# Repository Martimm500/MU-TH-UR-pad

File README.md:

# MU / TH / UR Pad

A 16 Key Macropad dedicated to honoring the ALIEN Franchise...

and also day to day use :)

This is my first ever contact with PCB design but still I wanted to make something professional and that would push all my skills, including the coding ones forward.

I set out on making the design resemble MU / TH / UR from the ALIEN Movies and games (hence the retro look).

**For more info about the design process check out my [Development Journal](https://blueprint.hackclub.com/projects/13398) or the [Markdown Backup](https://github.com/Martimm500/MU-TH-UR-pad/blob/main/mu-th-ur-pad-journal.md) of it!**

## Design

First it's extremely important to notice **I was heavily inspired by Orpheuspad** (literally as soon as I saw it I said "I gotta make something like this"), 

Second my goal was not to copy Orpheuspad, it was to make a PCB from the ground up, but keeping what the thing I really liked in the Orpheuspad case, I fixed some errors I encountered in it's 3D model, and adjusted some details to my preference.

The final product turned out as a **16 Key Macropad featuring an OLED Screen, a Rotary Encoder and 2 LEDs**. The left side of the case is a Orpheuspad Fix and Improvement while making the style a little bit more **retro**, and the right side is merely and expansion upon that.

The colors of the case resemble MU / TH / UR (and honestly those old office keyboards lol)

Finnally I added a Dither Art of a facehugger strangling a person on the back of the PCB as well as some references to the movies and the famous ALIEN slogan.

## BOM Table

Also available as a CSV file [BOM.csv](https://github.com/ppppp)!

|ITEM                                                                                                                                                                                                                                                                                                                                                                                                                                                                                                                                                                                                                                                                                                                                          |QTY                       |UNIT PRICE (USD)|TOTAL PRICE + SHIPPING + TAX (USD)|LINK                               |
|----------------------------------------------------------------------------------------------------------------------------------------------------------------------------------------------------------------------------------------------------------------------------------------------------------------------------------------------------------------------------------------------------------------------------------------------------------------------------------------------------------------------------------------------------------------------------------------------------------------------------------------------------------------------------------------------------------------------------------------------|--------------------------|----------------|----------------------------------|-----------------------------------|
|WAVESHARE  RP2040-Zero                                                                                                                                                                                                                                                                                                                                                                                                                                                                                                                                                                                                                                                                                                                        |1                         |3,99            |9,99                              |https://www.waveshare.com/rp2040-zero.htm?sku=20187|
|PCB                                                                                                                                                                                                                                                                                                                                                                                                                                                                                                                                                                                                                                                                                                                                           |1                         |29,6            |36,2                              |https://www.pcbway.com/            |
|0.91in OLED Display                                                                                                                                                                                                                                                                                                                                                                                                                                                                                                                                                                                                                                                                                                                           |1                         |4,05            |4,05                              |https://mauser.pt/096-8736/display-lcd-oled-0-91-128x32-ssd1306-branco|
|SK6812 MINI-E LEDs                                                                                                                                                                                                                                                                                                                                                                                                                                                                                                                                                                                                                                                                                                                            |10                 (minimum amount)|2,80            |3,00                              |https://pt.aliexpress.com/item/1005005237439694.html?spm=a2g0o.cart.0.0.f20f7f06EaY2LD&mp=1&pdp_npi=6%40dis%21EUR%21EUR%203.31%21EUR%202.42%21%21EUR%200.01%21%21%21%40211b612817743682508285298e4c09%2112000034757484069%21ct%21PT%214870840647%21%211%210%21&gatewayAdapt=glo2bra|
|M3x16mm Screws                                                                                                                                                                                                                                                                                                                                                                                                                                                                                                                                                                                                                                                                                                                                |10                        |2,43            |3,30                              |https://pt.aliexpress.com/item/1005008062349572.html?spm=a2g0o.cart.0.0.69cf7f06OGOyKT&mp=1&pdp_npi=6%40dis%21EUR%21EUR%202.95%21EUR%202.07%21%21EUR%200.66%21%21%21%40211b612817743685532634969e4c09%2112000043500292684%21ct%21PT%214870840647%21%211%210%21&gatewayAdapt=glo2bra|
|M3x5mx4mm Heatset Inserts                                                                                                                                                                                                                                                                                                                                                                                                                                                                                                                                                                                                                                                                                                                     |50                 (minimum amount)|3,07            |3,07                              |https://pt.aliexpress.com/item/1005003757960694.html?spm=a2g0o.productlist.main.7.1e482Qyt2QytmP&algo_pvid=bef40634-cf65-41c2-8a7f-46e2aff07f71&algo_exp_id=bef40634-cf65-41c2-8a7f-46e2aff07f71-27&pdp_ext_f=%7B%22order%22%3A%2284%22%2C%22eval%22%3A%221%22%2C%22fromPage%22%3A%22search%22%7D&pdp_npi=6%40dis%21EUR%212.60%212.60%21%21%2120.30%2120.30%21%402103894417745352565988153eada3%2112000027063916156%21sea%21PT%214870840647%21X%211%210%21n_tag%3A-29919%3Bd%3A46ad6c6b%3Bm03_new_user%3A-29895&curPageLogUid=Y2EpQmLReKqC&utparam-url=scene%3Asearch%7Cquery_from%3A%7Cx_object_id%3A1005003757960694%7C_p_origin_prod%3A#nav-specification|
|EC11 20mm D-Shaft                                                                                                                                                                                                                                                                                                                                                                                                                                                                                                                                                                                                                                                                                                                             |1                         |1,80            |1,80                              |https://pt.aliexpress.com/item/1005007644083514.html?spm=a2g0o.productlist.main.1.19ee3e1740431B&algo_pvid=c092fb10-96fe-46a3-8712-490290609c39&algo_exp_id=c092fb10-96fe-46a3-8712-490290609c39-8&pdp_ext_f=%7B%22order%22%3A%222426%22%2C%22spu_best_type%22%3A%22price%22%2C%22eval%22%3A%221%22%2C%22fromPage%22%3A%22search%22%7D&pdp_npi=6%40dis%21EUR%211.48%211.48%21%21%211.67%211.67%21%40211b876e17745366241393449e1e09%2112000041630839421%21sea%21PT%214870840647%21X%211%210%21n_tag%3A-29919%3Bd%3A46ad6c6b%3Bm03_new_user%3A-29895&curPageLogUid=64qdZ3Yt2uV0&utparam-url=scene%3Asearch%7Cquery_from%3A%7Cx_object_id%3A1005007644083514%7C_p_origin_prod%3A|
|1N4148 Through-Hole Diodes                                                                                                                                                                                                                                                                                                                                                                                                                                                                                                                                                                                                                                                                                                                    |20                        |1,14 (10 pcs)   |2,28                              |https://mauser.pt/007-0205/diodo-comutacao-100v-200ma-1n4148-sod27-do-35|
|Switch Kailh BOX White V2                                                                                                                                                                                                                                                                                                                                                                                                                                                                                                                                                                                                                                                                                                                     |20 (due to increments of 10)|5,15 (10pcs)    |10,30                             |https://pt.aliexpress.com/item/1005008965375077.html?spm=a2g0o.cart.0.0.69cf7f0654d5Ct&mp=1&pdp_npi=6%40dis%21EUR%21EUR%204.46%21EUR%204.46%21%21EUR%204.37%21%21%21%40210390c217745408586866266efd4e%2112000047395461126%21ct%21PT%214870840647%21%212%210%21&gatewayAdapt=glo2bra|
|XDA PBT Keycaps                                                                                                                                                                                                                                                                                                                                                                                                                                                                                                                                                                                                                                                                                                                               |20                        |2,36 (10pcs)    |4,71                              |https://pt.aliexpress.com/item/1005005514406952.html?spm=a2g0o.cart.0.0.69cf7f0654d5Ct&mp=1&pdp_npi=6%40dis%21EUR%21EUR%204.08%21EUR%204.08%21%21EUR%204.08%21%21%21%40210390c217745408586866266efd4e%2112000033372744419%21ct%21PT%214870840647%21%211%210%21&gatewayAdapt=glo2bra|
## Acknowledgements

 - [Hack Club](https://hackclub.com)
 - [Orpheuspad/Hackpad](https://github.com/hackclub/hackpad/)
 - [QMK](https://qmk.fm)

A BIG SHOUTOUT TO [@qcoral](https://github.com/qcoral)
## Authors

- [@Martimm500](https://www.github.com/Martimm500)

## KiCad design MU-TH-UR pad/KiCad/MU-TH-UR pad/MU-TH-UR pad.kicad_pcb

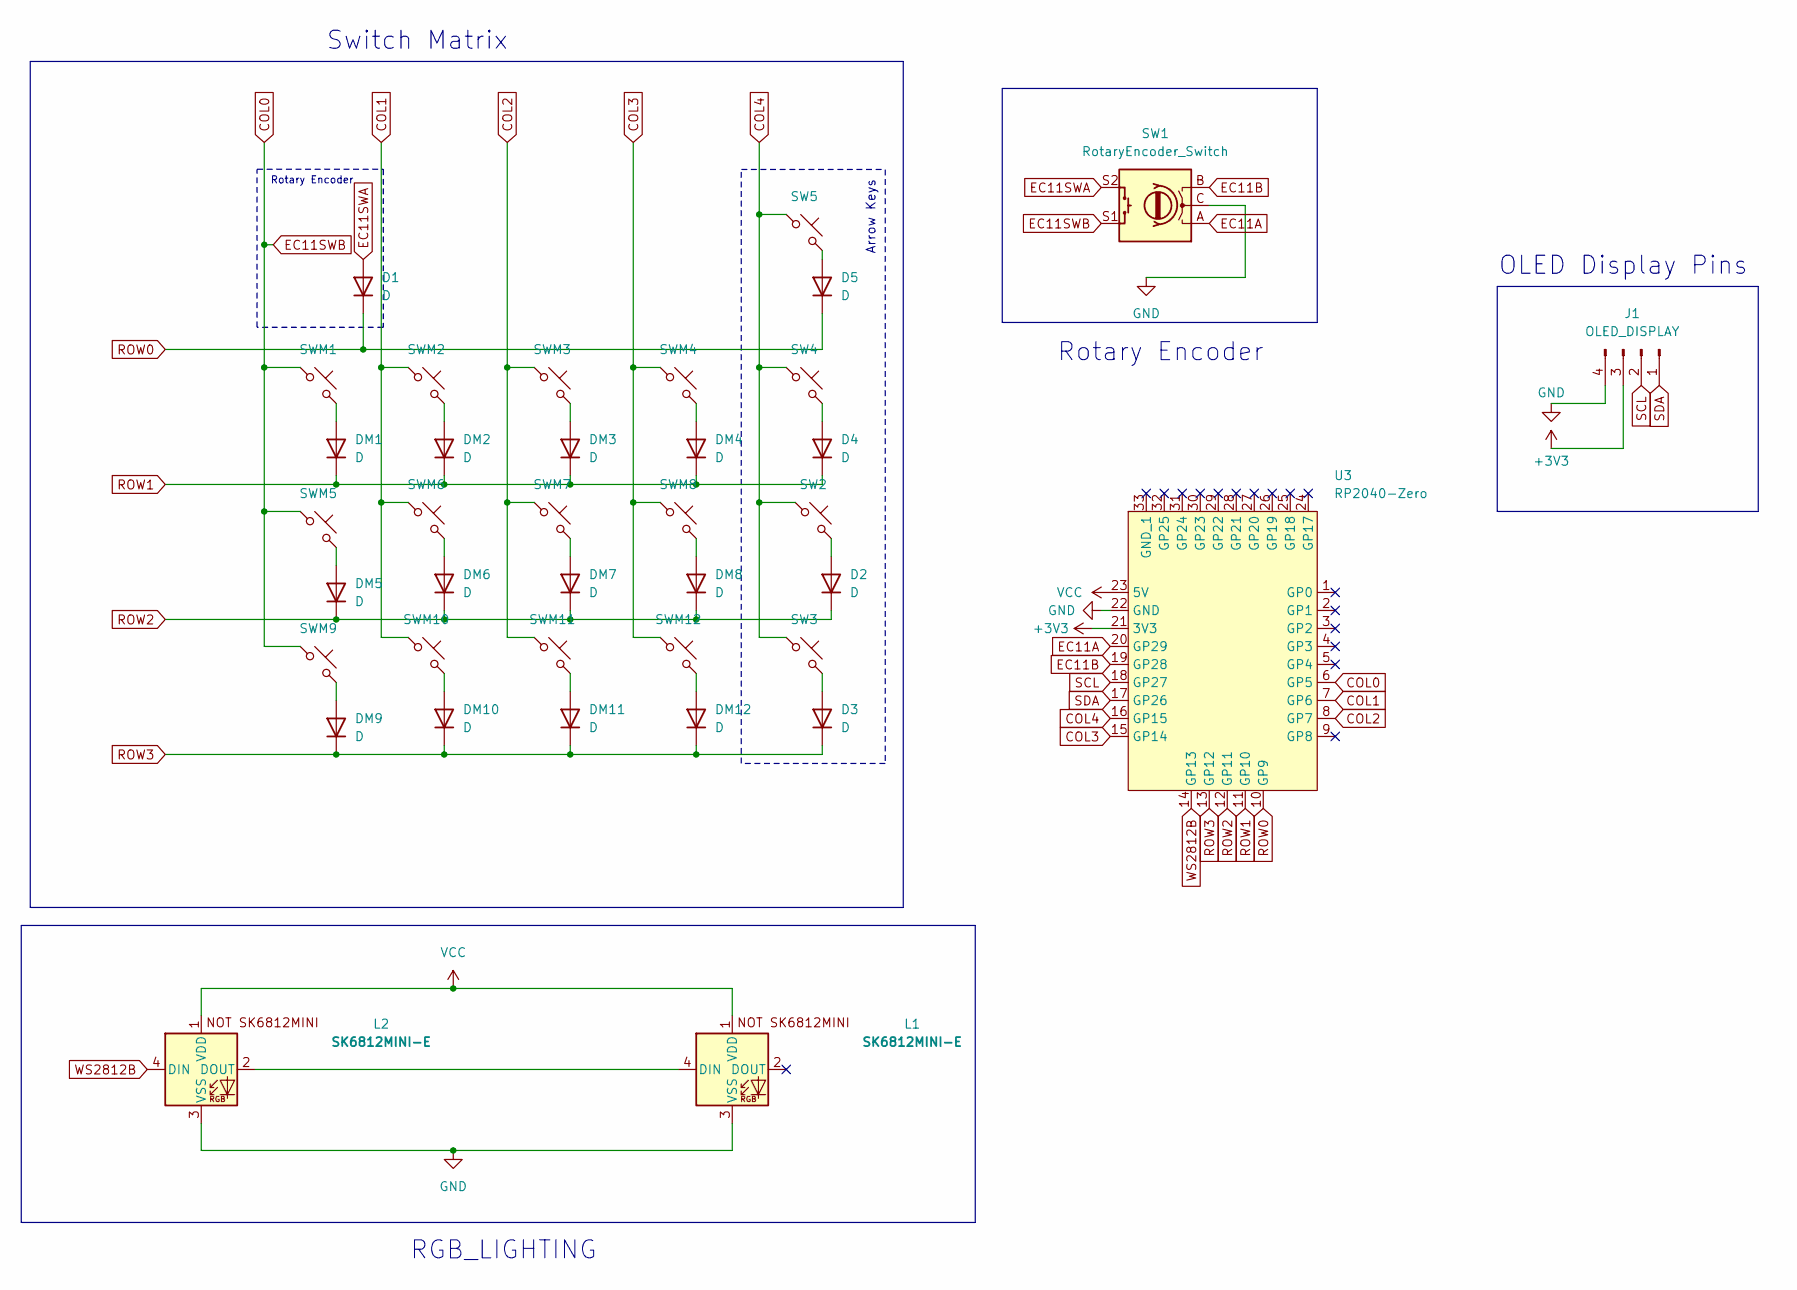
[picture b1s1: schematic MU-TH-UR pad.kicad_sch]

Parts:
D1, D2, D3, D4, D5: D; D_DO-35_SOD27_P7.62mm_Horizontal
DM1, DM2, DM3, DM4, DM5, DM6, DM7, DM8, DM9, DM10, DM11, DM12: D; D_DO-35_SOD27_P7.62mm_Horizontal
J1: OLED_DISPLAY; PinHeader_1x04_P2.54mm_Vertical
L1, L2: SK6812MINI-E; SK6812MINI-E_fixed
SW1: RotaryEncoder_Switch; RotaryEncoder_Alps_EC11E-Switch_Vertical_H20mm
SW2, SW3, SW4, SW5: SW_Push_45deg; MX-Solderable-1U
SWM1, SWM2, SWM3, SWM4, SWM5, SWM6, SWM7, SWM8, SWM9, SWM10, SWM11, SWM12: SW_Push_45deg; MX-Solderable-1U
U3: RP2040-Zero; RP2040-Zero-MUTHURV2

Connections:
+3V3: J1.3, U3.21 (3V3)
COL0: SW1.S1, SWM1.1, SWM5.1, SWM9.1, U3.6 (GP5)
COL1: SWM2.1, SWM6.1, SWM10.1, U3.7 (GP6)
COL2: SWM3.1, SWM7.1, SWM11.1, U3.8 (GP7)
COL3: SWM4.1, SWM8.1, SWM12.1, U3.15 (GP14)
COL4: SW2.1, SW3.1, SW4.1, SW5.1, U3.16 (GP15)
EC11A: SW1.A, U3.20 (GP29)
EC11B: SW1.B, U3.19 (GP28)
EC11SWA: D1.2 (A), SW1.S2
GND: J1.4, L1.3 (VSS), L2.3 (VSS), SW1.C, U3.22 (GND)
unnamed: D2.2 (A), SW2.2
unnamed: D3.2 (A), SW3.2
unnamed: D4.2 (A), SW4.2
unnamed: D5.2 (A), SW5.2
unnamed: DM1.2 (A), SWM1.2
unnamed: DM2.2 (A), SWM2.2
unnamed: DM3.2 (A), SWM3.2
unnamed: DM4.2 (A), SWM4.2
unnamed: DM5.2 (A), SWM5.2
unnamed: DM6.2 (A), SWM6.2
unnamed: DM7.2 (A), SWM7.2
unnamed: DM8.2 (A), SWM8.2
unnamed: DM9.2 (A), SWM9.2
unnamed: DM10.2 (A), SWM10.2
unnamed: DM11.2 (A), SWM11.2
unnamed: DM12.2 (A), SWM12.2
unnamed: L1.4 (DIN), L2.2 (DOUT)
ROW0: D1.1 (K), D5.1 (K), U3.10 (GP9)
ROW1: D4.1 (K), DM1.1 (K), DM2.1 (K), DM3.1 (K), DM4.1 (K), U3.11 (GP10)
ROW2: D2.1 (K), DM5.1 (K), DM6.1 (K), DM7.1 (K), DM8.1 (K), U3.12 (GP11)
ROW3: D3.1 (K), DM9.1 (K), DM10.1 (K), DM11.1 (K), DM12.1 (K), U3.13 (GP12)
SCL: J1.2, U3.18 (GP27)
SDA: J1.1, U3.17 (GP26)
VCC: L1.1 (VDD), L2.1 (VDD), U3.23 (5V)
WS2812B: L2.4 (DIN), U3.14 (GP13)

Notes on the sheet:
Rotary Encoder
RGB_LIGHTING
Arrow Keys
Switch Matrix
OLED Display Pins

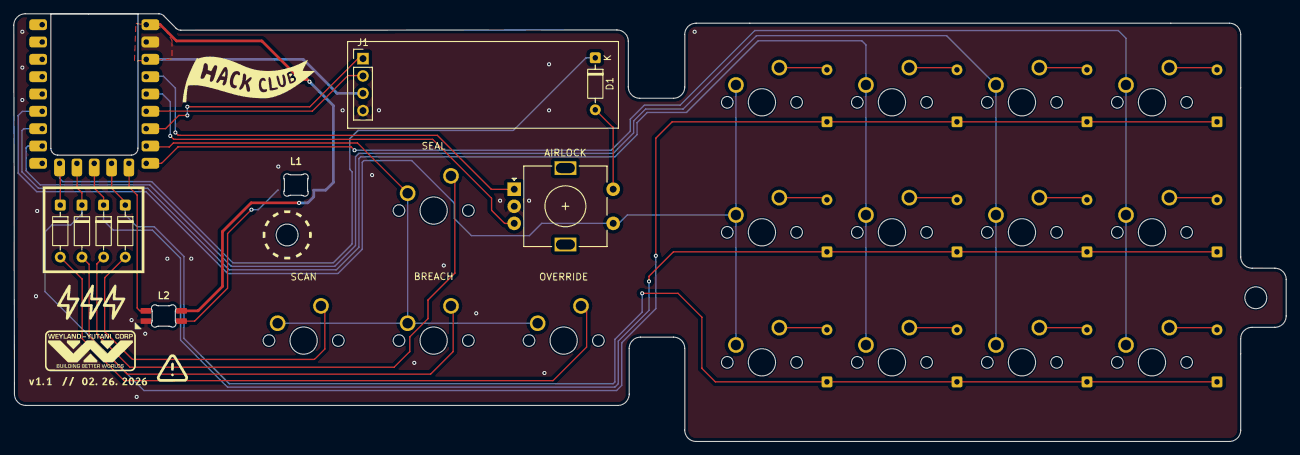
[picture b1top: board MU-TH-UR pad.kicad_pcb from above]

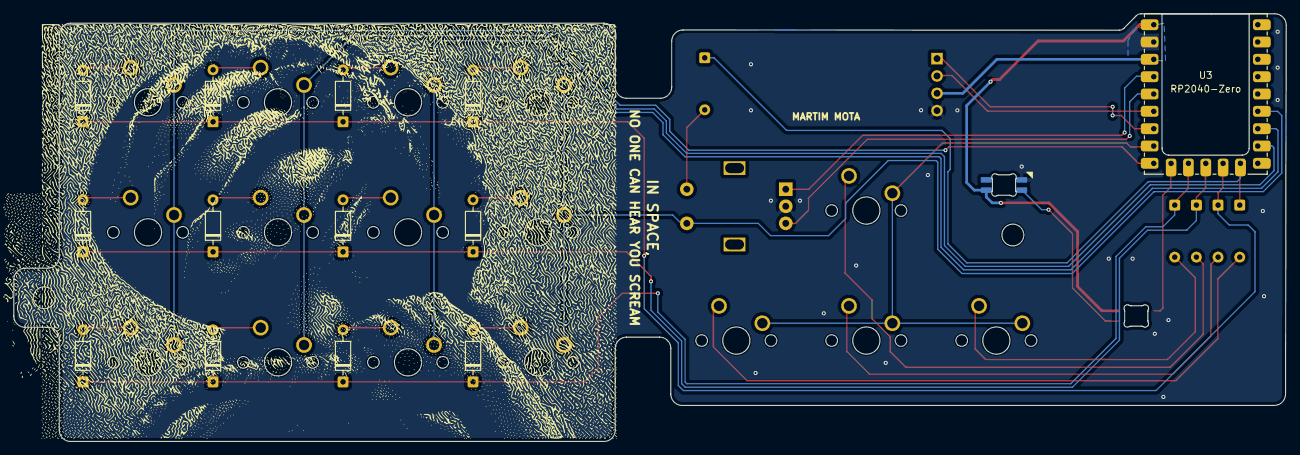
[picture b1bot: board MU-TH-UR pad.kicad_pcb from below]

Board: 2 copper layers, 186.4 x 62.6 mm, 38 parts (14 on the bottom side), 35 nets.

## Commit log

2026-03-26 Add All FIles
2026-03-26 Update Readme
    Updated image links in README to point to GitHub repository.
2026-03-27 Added Jounal in Markdown format as a backup
2026-03-27 Update README with additional journal link
2026-03-27 Updated the Full Step File to Include Eletronics
2026-04-27 Added f3z to comply with Blueprint requirements
2026-06-24 Fixed DRC Errors
2026-06-24 Fixed Edge Cut
2026-06-24 Added Serial Number Location for PCBWay
2026-06-24 JLCPCB Gerbers
